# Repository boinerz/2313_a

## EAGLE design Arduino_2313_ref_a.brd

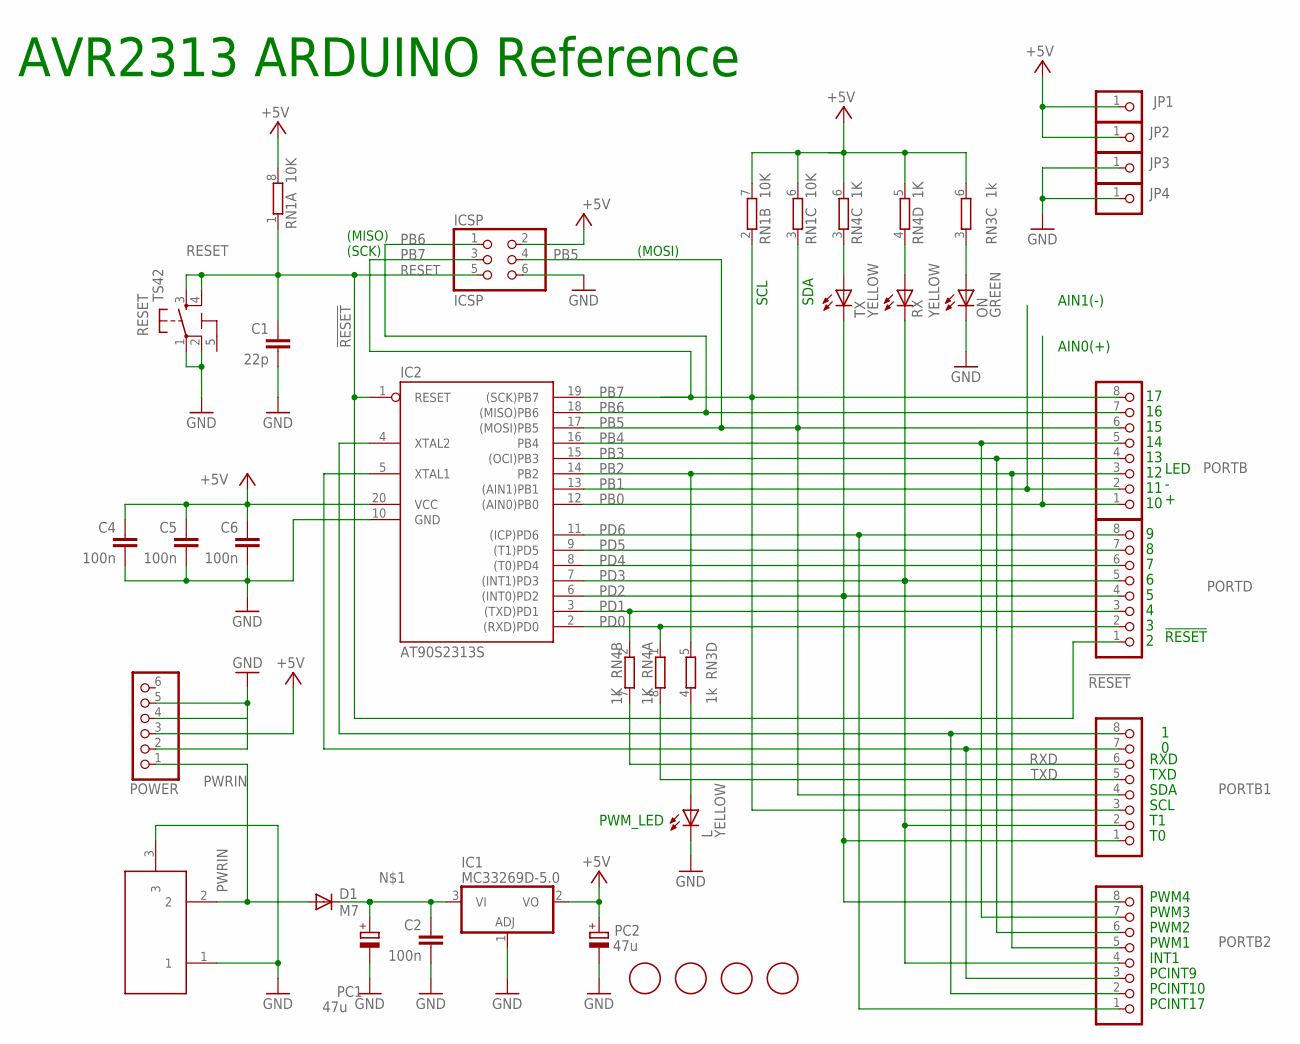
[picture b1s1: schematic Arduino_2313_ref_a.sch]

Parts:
C1: 22p; C0603-ROUND
C2, C4, C5, C6: 100n; C0603-ROUND
D1: M7; SMB
IC1: MC33269D-5.0; DPACK
IC2: AT90S2313S; SO20L
ICSP: ICSP; 2X03
JP1, JP2, JP3, JP4: PINHD-1X1; 1X01
L: YELLOW; CHIP-LED0805
ON: GREEN; CHIP-LED0805
PC1, PC2: 47u; PANASONIC_D
PORTB, PORTB1, PORTB2: PINHD-1X8; 1X08
PORTD: PINHD-1X8; 1X08
POWER: PINHD-1X6; 1X06
RESET: TS42
RN1: 10K; CAT16
RN3: 1k; CAY16
RN4: 1K; CAY16
RX: YELLOW; CHIP-LED0805
TX: YELLOW; CHIP-LED0805
U$2, U$3, U$4, U$5: FIDUCIALMOUNT; FIDUCIA-MOUNT
X1: DC21MMX; DC-21MM

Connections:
5-GND: RESET.5 (5-GND)
!RESET: IC2.1 (RESET), ICSP.5, PORTD.1
+5V: C4.1, C5.1, C6.1, IC1.2 (VO), IC2.20 (VCC), ICSP.2, JP1.1, JP2.1, PC2.+, POWER.3, RN1.6 (2), RN1.7 (2), RN1.8 (2), RN3.6 (2), RN4.5 (2), RN4.6 (2)
GND: C1.2, C2.2, C4.2, C5.2, C6.2, IC1.1 (ADJ), IC2.10 (GND), ICSP.6, JP3.1, JP4.1, L.C, ON.C, PC1.-, PC2.-, POWER.2, POWER.4, POWER.5, RESET.1, RESET.2, X1.1, X1.3
unnamed: C2.1, D1.C, IC1.3 (VI), PC1.+
unnamed: L.A, RN3.4 (1)
unnamed: ON.A, RN3.3 (1)
unnamed: RN4.4 (1), RX.A
unnamed: RN4.3 (1), TX.A
PA0: IC2.5 (XTAL1), PORTB1.7, PORTB2.3
PA1: IC2.4 (XTAL2), PORTB1.8, PORTB2.2
PB0: IC2.12 ((AIN0)PB0), PORTB.1
PB1: IC2.13 ((AIN1)PB1), PORTB.2
PB2: IC2.14 (PB2), PORTB.3, PORTB2.5, RN3.5 (2)
PB3: IC2.15 ((OCI)PB3), PORTB.4, PORTB2.6
PB4: IC2.16 (PB4), PORTB.5, PORTB2.7
PB5: IC2.17 ((MOSI)PB5), ICSP.4, PORTB.6, PORTB1.4, RN1.3 (1)
PB6: IC2.18 ((MISO)PB6), ICSP.1, PORTB.7
PB7: IC2.19 ((SCK)PB7), ICSP.3, PORTB.8, PORTB1.3, RN1.2 (1)
PD0: IC2.2 ((RXD)PD0), PORTD.2, RN4.1
PD1: IC2.3 ((TXD)PD1), PORTD.3, RN4.2 (1)
PD2: IC2.6 ((INT0)PD2), PORTB1.1, PORTB2.8, PORTD.4, TX.C
PD3: IC2.7 ((INT1)PD3), PORTB1.2, PORTB2.4, PORTD.5, RX.C
PD4: IC2.8 ((T0)PD4), PORTD.6
PD5: IC2.9 ((T1)PD5), PORTD.7
PD6: IC2.11 ((ICP)PD6), PORTB2.1, PORTD.8
PWRIN: D1.A, POWER.1, X1.2
RESET: C1.1, RESET.3, RESET.4, RN1.1
RXD: PORTB1.6, RN4.7 (2)
TXD: PORTB1.5, RN4.8 (2)

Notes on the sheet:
(MISO)
(SCK)
(MOSI)
AVR2313 ARDUINO Reference
SDA
SCL
!RESET
TXD
RXD
AIN0(+)
AIN1(-)
PCINT10
INT1
PWM1
PWM2
PWM3
PWM4
PCINT9
PCINT17
PWM_LED
LED

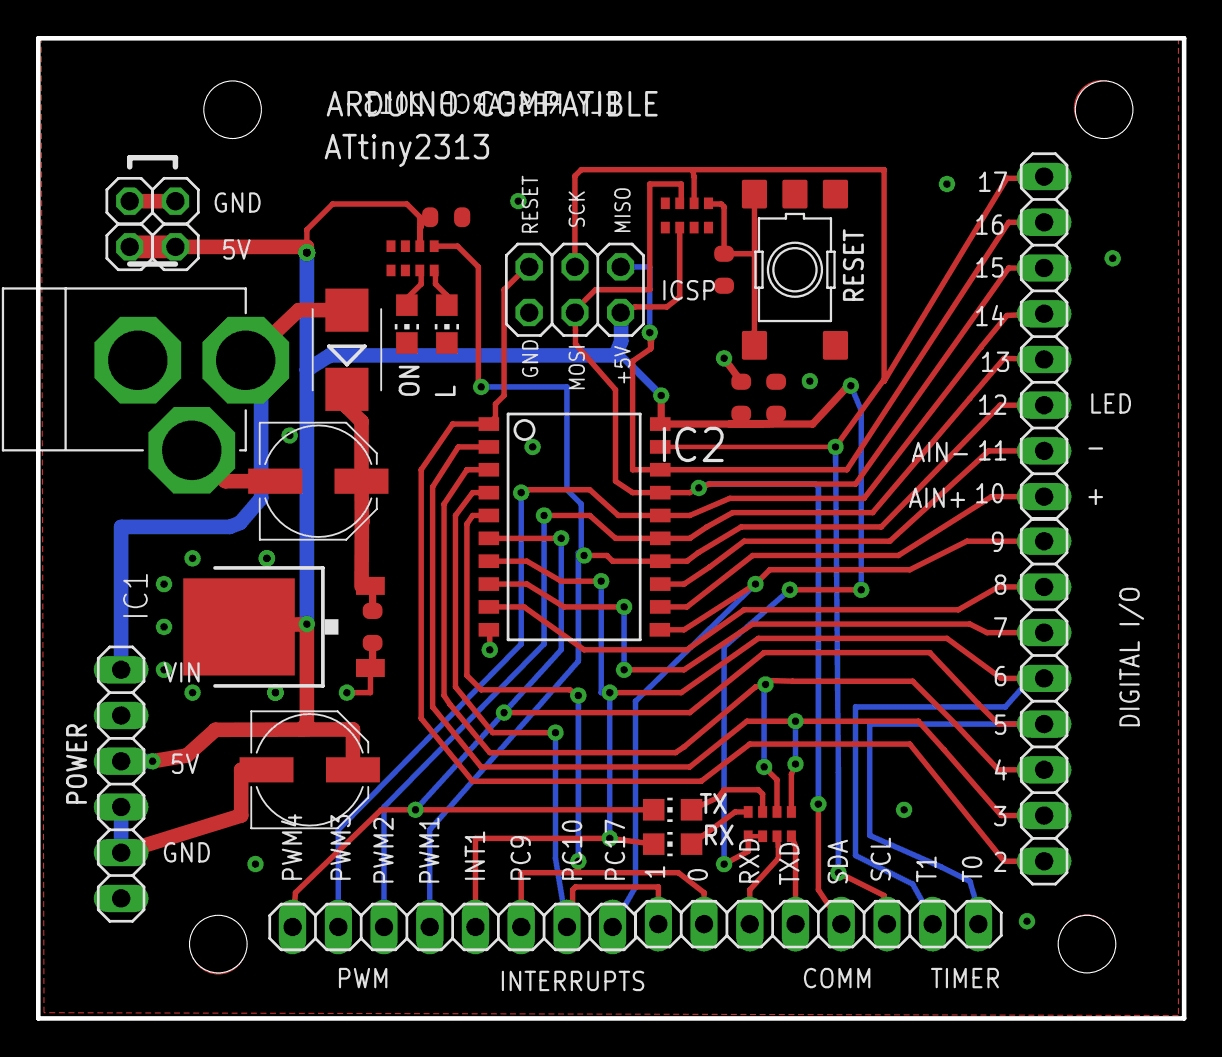
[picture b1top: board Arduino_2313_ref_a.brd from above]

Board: 2 copper layers, 63.7 x 54.5 mm, 33 parts (0 on the bottom side), 29 nets.

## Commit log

2013-04-30 2313 Arduino
    Has no USB, with labeled expansion for multi-use pins. Can be hand
    soldered. will ad support files.
